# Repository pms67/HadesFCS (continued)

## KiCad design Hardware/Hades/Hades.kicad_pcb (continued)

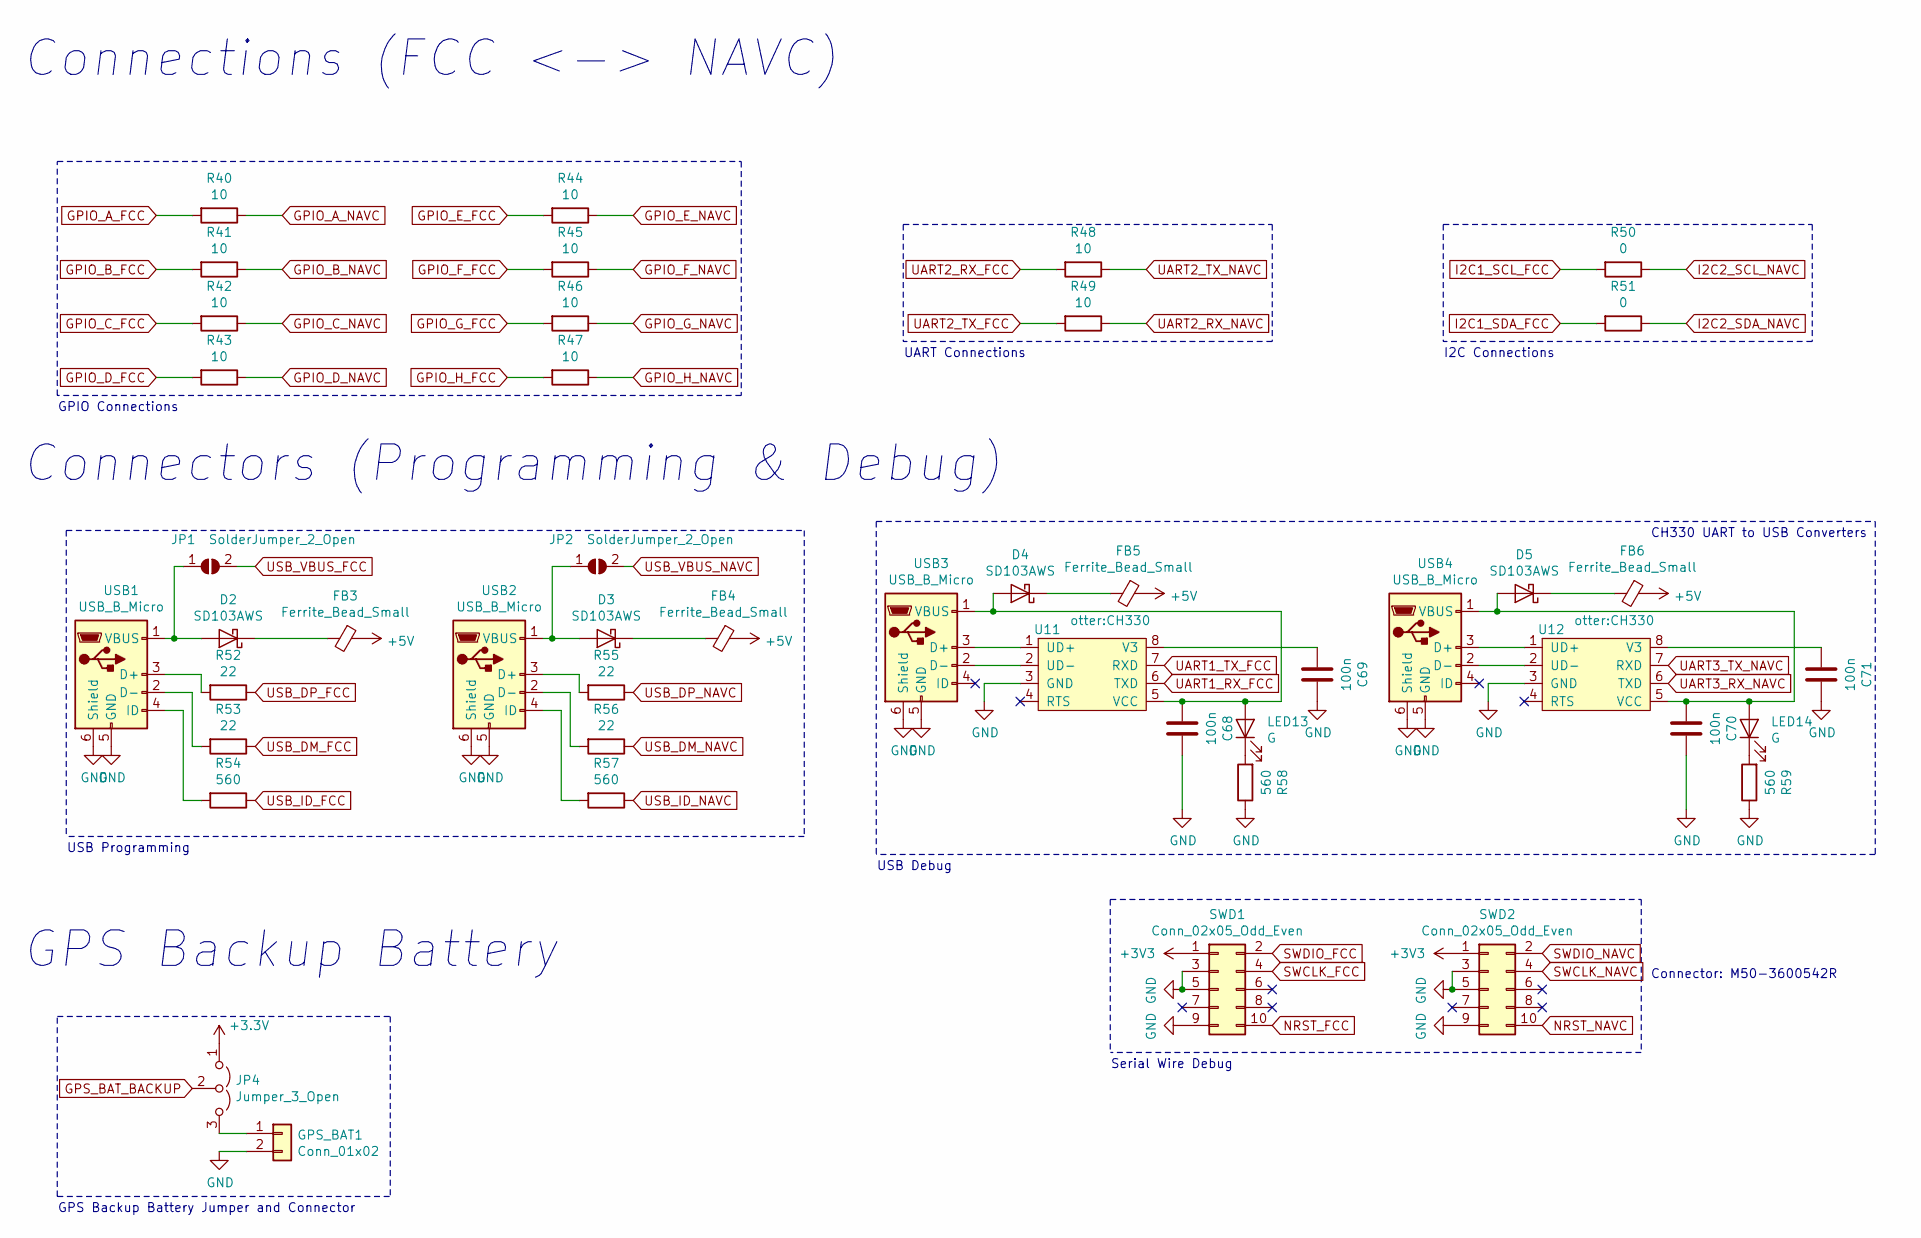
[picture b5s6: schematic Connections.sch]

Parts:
C68, C69, C70, C71: 100n; C_0402_1005Metric
D2, D3, D4, D5: SD103AWS; D_SOD-323
FB3, FB4, FB5, FB6: Ferrite_Bead_Small; L_0402_1005Metric
GPS_BAT1: Conn_01x02; Molex_PicoBlade_53048-0210_1x02_P1.25mm_Horizontal
JP1, JP2: SolderJumper_2_Open; SolderJumper-2_P1.3mm_Open_RoundedPad1.0x1.5mm
JP4: Jumper_3_Open; SolderJumper-3_P1.3mm_Open_RoundedPad1.0x1.5mm
LED13, LED14: G; LED_0603_1608Metric
R40, R41, R42, R43, R44, R45, R46, R47, R48, R49: 10; R_0402_1005Metric
R50, R51: 0; R_0603_1608Metric
R52, R53, R55, R56: 22; R_0402_1005Metric
R54, R57: 560; R_0402_1005Metric
R58, R59: 560; R_0603_1608Metric
SWD1, SWD2: Conn_02x05_Odd_Even; PinHeader_2x05_P1.27mm_Vertical_SMD
U11, U12: otter:CH330; SSOP-8_3.9x5.05mm_P1.27mm
USB1, USB2, USB3, USB4: USB_B_Micro; USB_Micro-B_Wuerth_629105150521_CircularHoles

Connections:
+5V: FB3.1, FB4.1, FB5.1, FB6.1; also elsewhere on the board
GND: C68.1, C69.1, C70.1, C71.1, GPS_BAT1.2, R58.1, R59.1, SWD1.3, SWD1.5, SWD1.9, SWD2.3, SWD2.5, SWD2.9, U11.3 (GND), U12.3 (GND), USB1.5 (GND), USB1.6 (Shield), USB2.5 (GND), USB2.6 (Shield), USB3.5 (GND), USB3.6 (Shield), USB4.5 (GND), USB4.6 (Shield); also elsewhere on the board
GPIO_A_FCC: R40.2; also elsewhere on the board
GPIO_A_NAVC: R40.1; also elsewhere on the board
GPIO_B_FCC: R41.2; also elsewhere on the board
GPIO_B_NAVC: R41.1; also elsewhere on the board
GPIO_C_FCC: R42.2; also elsewhere on the board
GPIO_C_NAVC: R42.1; also elsewhere on the board
GPIO_D_FCC: R43.2; also elsewhere on the board
GPIO_D_NAVC: R43.1; also elsewhere on the board
GPIO_E_FCC: R44.2; also elsewhere on the board
GPIO_E_NAVC: R44.1; also elsewhere on the board
GPIO_F_FCC: R45.2; also elsewhere on the board
GPIO_F_NAVC: R45.1; also elsewhere on the board
GPIO_G_FCC: R46.2; also elsewhere on the board
GPIO_G_NAVC: R46.1; also elsewhere on the board
GPIO_H_FCC: R47.2; also elsewhere on the board
GPIO_H_NAVC: R47.1; also elsewhere on the board
GPS_BAT_BACKUP: JP4.2 (C); also elsewhere on the board
I2C1_SCL_FCC: R50.2; also elsewhere on the board
I2C1_SDA_FCC: R51.2; also elsewhere on the board
I2C2_SCL_NAVC: R50.1; also elsewhere on the board
I2C2_SDA_NAVC: R51.1; also elsewhere on the board
unnamed: C68.2, D4.2 (A), LED13.2 (A), U11.5 (VCC), USB3.1 (VBUS)
unnamed: C69.2, U11.8 (V3)
unnamed: C70.2, D5.2 (A), LED14.2 (A), U12.5 (VCC), USB4.1 (VBUS)
unnamed: C71.2, U12.8 (V3)
unnamed: D2.1 (K), FB3.2
unnamed: D2.2 (A), JP1.1 (A), USB1.1 (VBUS)
unnamed: D3.1 (K), FB4.2
unnamed: D3.2 (A), JP2.1 (A), USB2.1 (VBUS)
unnamed: D4.1 (K), FB5.2
unnamed: D5.1 (K), FB6.2
unnamed 119: GPS_BAT1.1, JP4.3 (B); also elsewhere on the board
unnamed: LED13.1 (K), R58.2
unnamed: LED14.1 (K), R59.2
unnamed: R52.2, USB1.3 (D+)
unnamed: R53.2, USB1.2 (D-)
unnamed: R54.2, USB1.4 (ID)
unnamed: R55.2, USB2.3 (D+)
unnamed: R56.2, USB2.2 (D-)
unnamed: R57.2, USB2.4 (ID)
unnamed: SWD1.1, SWD2.1
unnamed: U11.1 (UD+), USB3.3 (D+)
unnamed: U11.2 (UD-), USB3.2 (D-)
unnamed: U12.1 (UD+), USB4.3 (D+)
unnamed: U12.2 (UD-), USB4.2 (D-)
UART1_RX_FCC: U11.6 (TXD); also elsewhere on the board
UART1_TX_FCC: U11.7 (RXD); also elsewhere on the board
UART2_RX_FCC: R48.2; also elsewhere on the board
UART2_RX_NAVC: R49.1; also elsewhere on the board
UART2_TX_FCC: R49.2; also elsewhere on the board
UART2_TX_NAVC: R48.1; also elsewhere on the board
UART3_RX_NAVC: U12.6 (TXD); also elsewhere on the board
UART3_TX_NAVC: U12.7 (RXD); also elsewhere on the board
USB_DM_FCC: R53.1; also elsewhere on the board
USB_DM_NAVC: R56.1; also elsewhere on the board
USB_DP_FCC: R52.1; also elsewhere on the board
USB_DP_NAVC: R55.1; also elsewhere on the board
USB_ID_FCC: R54.1; also elsewhere on the board
USB_ID_NAVC: R57.1; also elsewhere on the board
USB_VBUS_FCC: JP1.2 (B); also elsewhere on the board
USB_VBUS_NAVC: JP2.2 (B); also elsewhere on the board

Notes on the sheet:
GPIO Connections
UART Connections
I2C Connections
Connections (FCC <-> NAVC)
GPS Backup Battery
GPS Backup Battery Jumper and Connector
Connectors (Programming & Debug)
USB Programming
USB Debug
CH330 UART to USB Converters
Serial Wire Debug
Connector: M50-3600542R

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
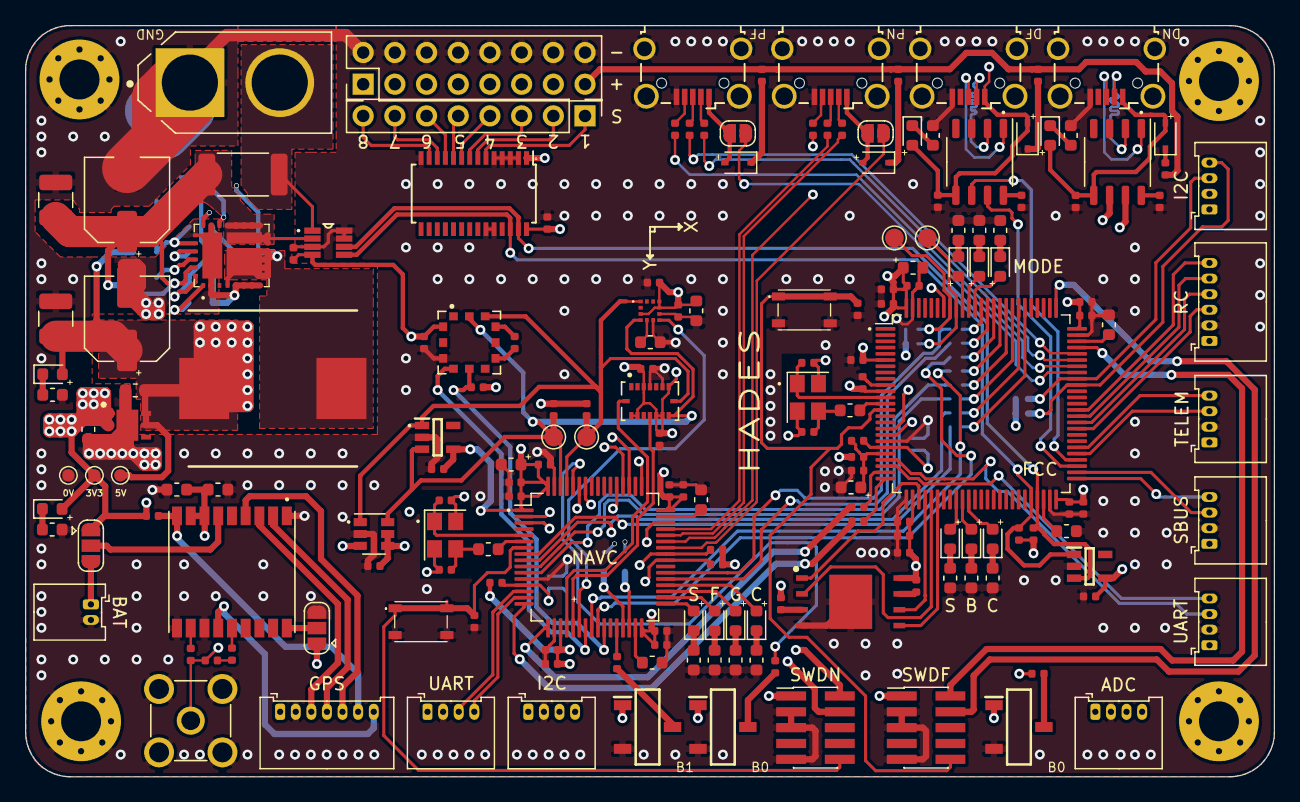
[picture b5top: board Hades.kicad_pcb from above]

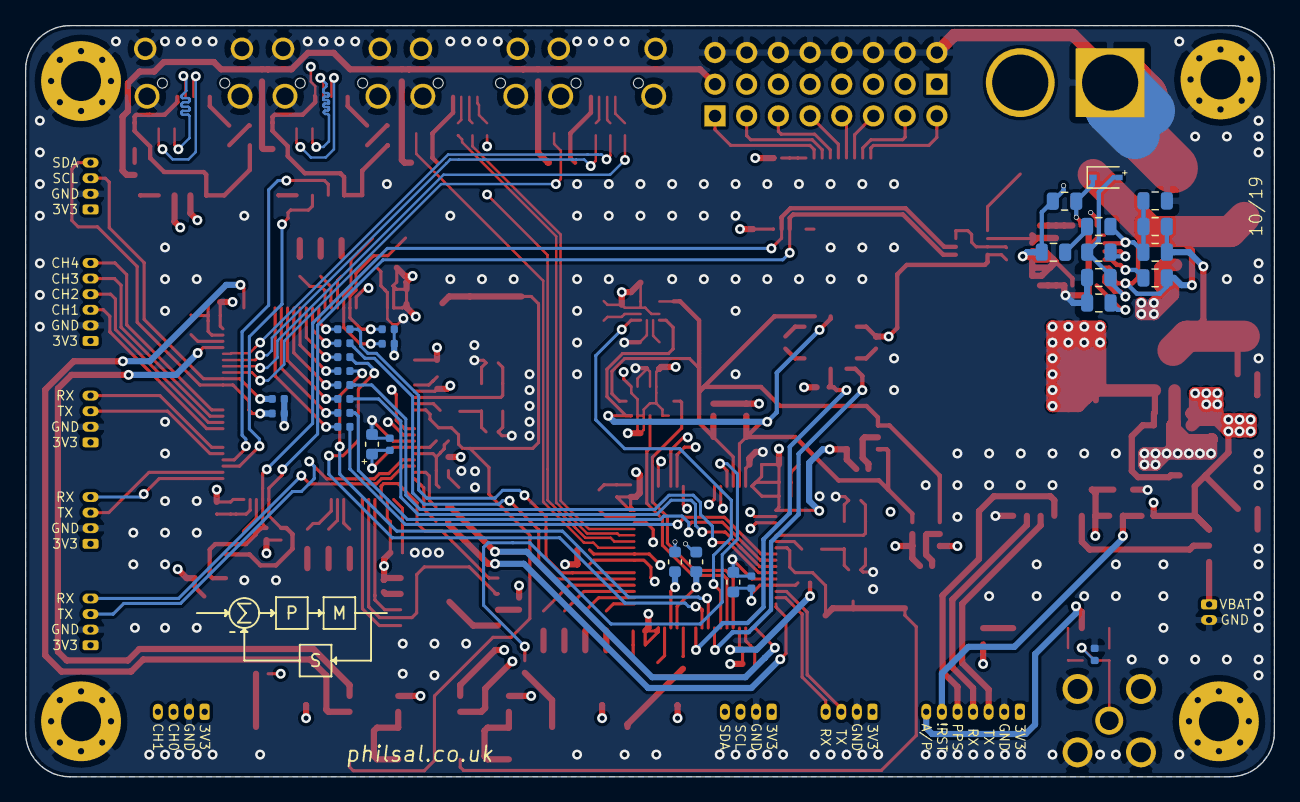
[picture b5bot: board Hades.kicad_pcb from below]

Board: 4 copper layers, 100.1 x 60.2 mm, 211 parts (30 on the bottom side), 174 nets.

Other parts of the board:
5V, 5V#2, 5V#3: TestPoint_Pad_D1.0mm
ADC: Conn_01x04; Molex_PicoBlade_53048-0410_1x04_P1.25mm_Horizontal
BAT: Conn_01x02; Molex_PicoBlade_53048-0210_1x02_P1.25mm_Horizontal
FCC: STM32H753VITx; LQFP-100_14x14mm_P0.5mm
GPS: Conn_01x07; Molex_PicoBlade_53048-0710_1x07_P1.25mm_Horizontal
I2C, I2C#2: Conn_01x04; Molex_PicoBlade_53048-0410_1x04_P1.25mm_Horizontal
NAVC: STM32F405RGTx; LQFP-64_10x10mm_P0.5mm
RC: Conn_01x06; Molex_PicoBlade_53048-0610_1x06_P1.25mm_Horizontal
SBUS: Conn_01x04; Molex_PicoBlade_53048-0410_1x04_P1.25mm_Horizontal
SWDF: Conn_02x05_Odd_Even; PinHeader_2x05_P1.27mm_Vertical_SMD
SWDN: Conn_02x05_Odd_Even; PinHeader_2x05_P1.27mm_Vertical_SMD
TELEM: Conn_01x04; Molex_PicoBlade_53048-0410_1x04_P1.25mm_Horizontal
UART: Conn_01x04; Molex_PicoBlade_53048-0410_1x04_P1.25mm_Horizontal
UART#2: Conn_01x04; Molex_PicoBlade_53048-0410_1x04_P1.25mm_Horizontal

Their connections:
+5V: 5V#3.1; also elsewhere on the board
ADC3_0_FCC: ADC.3, FCC.17
ADC3_1_FCC: ADC.4, FCC.18
BAR_NRST_NAVC: NAVC.26; also elsewhere on the board
BOOT0_FCC: FCC.94; also elsewhere on the board
BOOT0_NAVC: NAVC.60; also elsewhere on the board
BOOT1_NAVC: NAVC.28; also elsewhere on the board
GND: 5V.1, ADC.2, BAT.2, FCC.10, FCC.19, FCC.26, FCC.49, FCC.74, FCC.99, GPS.2, I2C.2, I2C#2.2, NAVC.12, NAVC.18, NAVC.63, RC.2, SBUS.2, SWDF.3, SWDF.5, SWDF.9, SWDN.3, SWDN.5, SWDN.9, TELEM.2, UART.2, UART#2.2; also elsewhere on the board
GPIO_A_FCC: FCC.81; also elsewhere on the board
GPIO_A_NAVC: NAVC.8; also elsewhere on the board
GPIO_B_FCC: FCC.82; also elsewhere on the board
GPIO_B_NAVC: NAVC.9; also elsewhere on the board
GPIO_C_FCC: FCC.83; also elsewhere on the board
GPIO_C_NAVC: NAVC.10; also elsewhere on the board
GPIO_D_FCC: FCC.84; also elsewhere on the board
GPIO_D_NAVC: NAVC.11; also elsewhere on the board
GPIO_E_FCC: FCC.85; also elsewhere on the board
GPIO_E_NAVC: NAVC.24; also elsewhere on the board
GPIO_F_FCC: FCC.86; also elsewhere on the board
GPIO_F_NAVC: NAVC.25; also elsewhere on the board
GPIO_G_FCC: FCC.87; also elsewhere on the board
GPIO_G_NAVC: NAVC.37; also elsewhere on the board
GPIO_H_FCC: FCC.88; also elsewhere on the board
GPIO_H_NAVC: NAVC.38; also elsewhere on the board
GPS_LNA_EN_NAVC: GPS.7, NAVC.2; also elsewhere on the board
GPS_NRST_NAVC: GPS.6, NAVC.3; also elsewhere on the board
GPS_PPS_NAVC: GPS.5, NAVC.53; also elsewhere on the board
HSE_IN_FCC: FCC.12; also elsewhere on the board
HSE_IN_NAVC: NAVC.5; also elsewhere on the board
HSE_OUT_FCC: FCC.13; also elsewhere on the board
HSE_OUT_NAVC: NAVC.6; also elsewhere on the board
I2C1_SCL_FCC: FCC.92; also elsewhere on the board
I2C1_SCL_NAVC: NAVC.61; also elsewhere on the board
I2C1_SDA_FCC: FCC.93; also elsewhere on the board
I2C1_SDA_NAVC: NAVC.62; also elsewhere on the board
I2C2_SCL_FCC: FCC.46; also elsewhere on the board
I2C2_SCL_NAVC: NAVC.29; also elsewhere on the board
I2C2_SDA_FCC: FCC.47; also elsewhere on the board
I2C2_SDA_NAVC: NAVC.30; also elsewhere on the board
I2C3_SCL_FCC: FCC.67, I2C.3; also elsewhere on the board
I2C3_SCL_NAVC: I2C#2.3, NAVC.41; also elsewhere on the board
I2C3_SDA_FCC: FCC.66, I2C.4; also elsewhere on the board
I2C3_SDA_NAVC: I2C#2.4, NAVC.40; also elsewhere on the board
INT_ACC_NAVC: NAVC.20; also elsewhere on the board
INT_BAR_NAVC: NAVC.23; also elsewhere on the board
INT_GYR_NAVC: NAVC.21; also elsewhere on the board
INT_MAG_NAVC: NAVC.22; also elsewhere on the board
LED_A_FCC: FCC.34; also elsewhere on the board
LED_A_NAVC: NAVC.33; also elsewhere on the board
LED_B_FCC: FCC.35; also elsewhere on the board
LED_B_NAVC: NAVC.34; also elsewhere on the board
LED_C_FCC: FCC.36; also elsewhere on the board
LED_C_NAVC: NAVC.35; also elsewhere on the board
LED_D_FCC: FCC.89; also elsewhere on the board
LED_D_NAVC: NAVC.36; also elsewhere on the board
LED_E_FCC: FCC.90; also elsewhere on the board
LED_F_FCC: FCC.91; also elsewhere on the board
NRST_FCC: FCC.14, SWDF.10; also elsewhere on the board
NRST_NAVC: NAVC.7, SWDN.10; also elsewhere on the board
unnamed 65: FCC.48; also elsewhere on the board
unnamed 66: FCC.73; also elsewhere on the board
unnamed 68: NAVC.31; also elsewhere on the board
unnamed 69: NAVC.47; also elsewhere on the board
unnamed 119: BAT.1; also elsewhere on the board
SPI1_CS_FLASH_FCC: FCC.28; also elsewhere on the board
SPI1_MISO_FCC: FCC.30; also elsewhere on the board
SPI1_MOSI_FCC: FCC.31; also elsewhere on the board
SPI1_SCK_FCC: FCC.29; also elsewhere on the board
SWCLK_FCC: FCC.76, SWDF.4
SWCLK_NAVC: NAVC.49, SWDN.4
SWDIO_FCC: FCC.72, SWDF.2
SWDIO_NAVC: NAVC.46, SWDN.2
TIM4_CH1_FCC: FCC.59, RC.3
TIM4_CH2_FCC: FCC.60, RC.4
TIM4_CH3_FCC: FCC.61, RC.5
TIM4_CH4_FCC: FCC.62, RC.6
UART1_RX_FCC: FCC.54; also elsewhere on the board
UART1_RX_NAVC: GPS.4, NAVC.59; also elsewhere on the board
UART1_TX_FCC: FCC.53; also elsewhere on the board
UART1_TX_NAVC: GPS.3, NAVC.58; also elsewhere on the board
UART2_RX_FCC: FCC.25; also elsewhere on the board
UART2_RX_NAVC: NAVC.17; also elsewhere on the board
UART2_TX_FCC: FCC.24; also elsewhere on the board
UART2_TX_NAVC: NAVC.16; also elsewhere on the board
UART3_RX_FCC: FCC.56, TELEM.4
UART3_RX_NAVC: NAVC.52; also elsewhere on the board
UART3_TX_FCC: FCC.55, TELEM.3
UART3_TX_NAVC: NAVC.51; also elsewhere on the board
UART4_RX_FCC: FCC.23, UART.4
UART4_RX_NAVC: NAVC.15, UART#2.4
UART4_TX_FCC: FCC.22, UART.3
UART4_TX_NAVC: NAVC.14, UART#2.3
UART5_RX_FCC: FCC.51, SBUS.4
UART5_TX_FCC: FCC.52, SBUS.3
USB_DM_FCC: FCC.70; also elsewhere on the board
USB_DM_NAVC: NAVC.44; also elsewhere on the board
USB_DP_FCC: FCC.71; also elsewhere on the board
USB_DP_NAVC: NAVC.45; also elsewhere on the board
USB_ID_FCC: FCC.69; also elsewhere on the board
USB_ID_NAVC: NAVC.43; also elsewhere on the board
USB_VBUS_FCC: FCC.68; also elsewhere on the board
USB_VBUS_NAVC: NAVC.42; also elsewhere on the board
VDDA_FCC: FCC.21; also elsewhere on the board
VDDA_NAVC: NAVC.13; also elsewhere on the board
VREF+_FCC: FCC.20; also elsewhere on the board

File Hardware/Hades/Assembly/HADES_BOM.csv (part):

Ref Des,Qty,Manufacturer,Mfr Part #,Value,Package,Type,Your Instructions / Notes
ANT1,1,TE Connectivity,5-1814832-1,5-1814832-1,5-1814832-1:TE_5-1814832-1,THT,"50 Ohm SMA, see 3D picture for orientation"
BAT1,1,SparkFun,PRT-10474,XT60-M,XT60-M:AMASS_XT60-M,THT,"Male XT-60 Connector, NEGATIVE TERMINAL indicated by DOT on silkscreen, SEE 3D PICTURE FOR REFERENCE!"
"C1, C8",2,Panasonic,EEE-FPV101XAV,100u,Capacitor_SMD:C_Elec_6.3x7.7,SMD,"Low ESR, High Ripple Current, Al Electrolytic, 35V, Polarity indicated by + on silkscreen"
"C2, C9",2,Taiyo Yuden,GMK325BJ226MM-T,22u,Capacitor_SMD:C_1210_3225Metric,SMD,"Low ESR, 35V"
"C3, C4",2,KEMET,C0805C225K4REC7210,2u2,Capacitor_SMD:C_0805_2012Metric,SMD,at least 10V rated
"C5, C6",2,KEMET,C0805X104K5RAC3316,100n,Capacitor_SMD:C_0805_2012Metric,SMD,at least 10V rated
C7,1,KEMET,C0805C472J3GEC7210,4n7,Capacitor_SMD:C_0805_2012Metric,SMD,at least 10V rated
"C10, C16, C17, C18, C19, C20, C21, C22, C23, C24, C25, C26, C28, C30, C31, C34, C35, C36, C40, C41, C42, C43, C44, C45, C46, C47, C48, C49, C51, C54, C55, C56, C58, C60, C61, C63, C68, C69, C70, C71, ",40,Murata Electronics,GRM155R61H104JE14D,100n,Capacitor_SMD:C_0402_1005Metric,SMD,at least 10V rated
"C11, C12, C62",3,Murata Electronics,GRM188R61E106KA73D,10u,Capacitor_SMD:C_0603_1608Metric,SMD,at least 10V rated
"C15, C39",2,AVX,F381A106MMAAH1,10u,Capacitor_SMD:C_0603_1608Metric,SMD,"Tantalum, Polarity indicated by + on silkscreen"
"C13, C14,  C37, C38,",4,Yageo,CC0603KRX5R9BB225,2u2,Capacitor_SMD:C_0603_1608Metric,SMD,ESR < 100mOhms!
"C27, C29, C50",3,AVX,TACL105K010RTA,1u,Capacitor_SMD:C_0603_1608Metric,SMD,"Tantalum, Polarity indicated by + on silkscreen"
"C64, C65",2,KEMET,C0603C105Z3VACTU,1u,Capacitor_SMD:C_0603_1608Metric,SMD,at least 10V rated
"C32, C33, C52, C53, ",4,AVX,04025A100JAT2A,10p,Capacitor_SMD:C_0402_1005Metric,SMD,at least 10V rated
"C57, ",1,KEMET,C0402C102J5GAC7411,1n,Capacitor_SMD:C_0402_1005Metric,SMD,at least 10V rated
"C59, ",1,KEMET,C0603C224K4RAC7411,220n,Capacitor_SMD:C_0603_1608Metric,SMD,at least 10V rated
C66,1,KEMET,C0402C220J8GACTU,22p,Capacitor_SMD:C_0402_1005Metric,SMD,at least 10V rated
"C67, ",1,KEMET,C0402C103J3RACAUTO,10n,Capacitor_SMD:C_0402_1005Metric,SMD,at least 10V rated
"D1, D2, D3, D5, D4, ",5,Diodes Incorporated,SD103AWS-7-F,SD103AWS,Diode_SMD:D_SOD-323,SMD,"Schottky diode, Polarity indicated by + on silkscreen"
"FB1, FB2, FB3, FB4, FB5, FB6, ",6,TDK,MPZ1005S121HT000,Ferrite_Bead_Small,Inductor_SMD:L_0402_1005Metric,SMD,"Ferrite bead, 1.5A current rating"
"FCC1, ",1,STMicroelectronics,STM32H753VIT6,STM32H753VITx,Package_QFP:LQFP-100_14x14mm_P0.5mm,SMD,"Pin 1 indicated by DOT on silkscreen, WATCH FOR PIN 1 ON DATASHEET (LQFP-100)"
"GPS_BAT1, ",1,Molex,53048-0210,Conn_01x02,Connector_Molex:Molex_PicoBlade_53048-0210_1x02_P1.25mm_Horizontal,THT,Watch orientation! See attached 3D picture!
"GPS_NAVC1, ",1,Molex,53048-0710,Conn_01x07,Connector_Molex:Molex_PicoBlade_53048-0710_1x07_P1.25mm_Horizontal,THT,Watch orientation! See attached 3D picture!
"HSE1, HSE2",2,ABRACON,ABM8G-25.000MHZ-4Y-T3,25MHz,Crystal:Crystal_SMD_Abracon_ABM8G-4Pin_3.2x2.5mm,SMD,"Pin 1 indicated by DOT on silkscreen, WATCH FOR PIN 1 ON DATASHEET"
L1,1,Bourns,SRP1265A-150M,15u,SRP1265A-150M:INDPM135125X650N,SMD,DC Current Rating at least 9A
L2,1,Murata Electronics,LQW15AN27NJ8ZD,27n,Inductor_SMD:L_0402_1005Metric,SMD,
"LED1, LED2, LED13, LED14, ",4,Dialight,599-0081-007F,GREEN,LED_SMD:LED_0603_1608Metric,SMD,"Green LED, Polarity indicated by + on silkscreen"
"LED3, LED4, LED9, LED10, ",4,Dialight,599-0010-007F,RED,LED_SMD:LED_0603_1608Metric,SMD,"Red LED, Polarity indicated by + on silkscreen"
"LED5, LED11, ",2,Dialight,599-0040-007F,YELLOW,LED_SMD:LED_0603_1608Metric,SMD,"Yellow LED, Polarity indicated by + on silkscreen"
"LED6, LED7, LED8, LED12, ",4,Dialight,599-0091-007F,BLUE,LED_SMD:LED_0603_1608Metric,SMD,"Blue LED, Polarity indicated by + on silkscreen"
"NAVC1, ",1,STMicroelectronics,STM32F405RGT6,STM32F405RGTx,Package_QFP:LQFP-64_10x10mm_P0.5mm,SMD,"Pin 1 indicated by DOT on silkscreen, WATCH FOR PIN 1 ON DATASHEET (LQFP-64)"
"PWM_POW1, ",1,Samtec,HTSW-108-07-T-T,Conn_02x08_Odd_Even,Connector_PinHeader_2.54mm:PinHeader_2x08_P2.54mm_Vertical,THT,"3 Rows 8 Columns (24 Positions total), 2.54mm Pitch, Vertical Male Header Pins"
"R1, ",1,Yageo,PE2512FKE7W0R01Z,0.01,Resistor_SMD:R_2512_6332Metric,SMD,1W 1% 10mOhms 2512 Current Sense Resistor
"R2, R3, ",2,Panasonic,ERJ-T06J103V,10k,Resistor_SMD:R_0805_2012Metric,SMD,1/4W
"R4, ",1,Panasonic,ERJ-PB6B1962V,19k6,Resistor_SMD:R_0805_2012Metric,SMD,"1%, 1/8W"
"R5, ",1,KOA Speer,RK73H2ATTD6R80F,6k8,Resistor_SMD:R_0805_2012Metric,SMD,"1%, 1/8W"
"R6, ",1,KOA Speer,RK73H2ATTD1301F,1k3,Resistor_SMD:R_0805_2012Metric,SMD,"1%, 1/8W"
"R7, R58, R59, ",3,Panasonic,ERJ-PA3F5600V,560,Resistor_SMD:R_0603_1608Metric,SMD,1/4W
"R8, ",1,Panasonic,ERJ-PA3F2400V,240,Resistor_SMD:R_0603_1608Metric,SMD,1/4W
"R9, R10, R11, R12, R13, R14, R28, R29, R30, R31, ",10,KOA Speer,SG73P1ETTP4701F,4k7,Resistor_SMD:R_0402_1005Metric,SMD,1/4W
"R15, R16, R17, R33, R34, R35, ",6,Panasonic,ERJ-PA3D3300V,330,Resistor_SMD:R_0603_1608Metric,SMD,1/4W
"R18, R19, R20, R36, ",4,Panasonic,ERJ-PA3D1000V,100,Resistor_SMD:R_0603_1608Metric,SMD,1/4W
"R21, ",1,Panasonic,ERA-2AED470X,47,Resistor_SMD:R_0402_1005Metric,SMD,1/8W
"R22, R24, R25, R26, R27, R37, R38, ",7,TE Connectivity / Holsworthy,CRGP0402F10K,10k,Resistor_SMD:R_0402_1005Metric,SMD,1/4W
"R23, R32, ",2,Panasonic,ERJ-PA3F6200V,620,Resistor_SMD:R_0603_1608Metric,SMD,1/4W
"R39, R40, R41, R42, R43, R44, R45, R46, R47, R48, R49, ",11,Panasonic,ERA-2AKD100X,10,Resistor_SMD:R_0402_1005Metric,SMD,1/8W
"R50, R51, ",2,Vishay / Dale,RCS06030000Z0EC,0,Resistor_SMD:R_0603_1608Metric,SMD,1/8W
"R52, R53, R55, R56, ",4,Panasonic,ERA-2AKD220X,22,Resistor_SMD:R_0402_1005Metric,SMD,1/8W
"R54, R57, ",2,TE Connectivity / Holsworthy,CRGP0402F560R,560,Resistor_SMD:R_0402_1005Metric,SMD,1/8W
"RCIN_FCC1, ",1,Molex,53048-0610,Conn_01x06,Connector_Molex:Molex_PicoBlade_53048-0610_1x06_P1.25mm_Horizontal,THT,Watch orientation! See attached 3D picture!
"REG1, ",1,Microchip Technology,MIC26903YJL-TR,MIC26903YJL-TR,MLF-28,SMD,Pin 1 indicated by DOT on silkscreen
"REG2, ",1,STMicroelectronics,LD39200PU33R,LD39200PU33R,DFN-6,SMD,Pin 1 indicated by DOT on silkscreen
"SW1, SW5, ",2,ALPS,SKRPANE010,SKRPANE010,SKRPANE010:SKRPADE010,SMD,See attached 3D picture for orientation
"SW2, SW3, SW4, ",3,C&K,TDD01H0SB1R,TDD01H0SB1R,TDD01H0SB1R:SOT175P420X230-3N,SMD,See attached 3D picture for orientation
"SWD1, SWD2, ",2,Harwin,M50-3600542R,Conn_02x05_Odd_Even,Connector_PinHeader_1.27mm:PinHeader_2x05_P1.27mm_Vertical_SMD,SMD,"2 Rows, 5 Columns (10 Positions), SMD 1.27mm pitch, See attached 3D picture for orientation"
"U1, ",1,Texas Instruments,INA219AIDCNR,INA219AIDCNR,SOT-23-8,SMD,Pin 1 indicated by DOT on silkscreen
"U2, ",1,NXP Semiconductors,"PCA9685PW,118",PCA9685PW,TSSOP28,SMD,Pin 1 indicated by DOT on silkscreen
"U3, U9, ",2,Microchip Technology,24CW1280T-I/OT,24CW1280T-I_OT,SOT-23-5,SMD,Pin 1 indicated by DOT on silkscreen
"U4, ",1,Winbond,W25N01GVZEIG TR,W25N01GVZEIG_TR,WSON 8x6-mm ,SMD,Pin 1 indicated by DOT on silkscreen
"U5, ",1,Bosch Sensortec,BMI088,BMI088,LGA-16,SMD,Pin 1 indicated by DOT on silkscreen
"U6, ",1,Texas Instruments,TMP100NA/3K,TMP100,SOT-23-6,SMD,Pin 1 indicated by DOT on silkscreen
"U7, ",1,Honeywell,MPRLS0025PA00001A,MPRLS0025PA00001A,MPRLS0025PA00001A:XDCR_MPRLS0025PA00001A,SMD,Pin 1 indicated by DOT on silkscreen
"U8, ",1,STMicroelectronics,IIS2MDCTR,IIS2MDCTR,LGA-12 2.0 x 2.0 x 0.7 mm,SMD,Pin 1 indicated by DOT on silkscreen
"U10, ",1,u-blox,MAX-8Q,u-blox MAX-8Q,MODULE-GPS-SMD-MAX-7Q-0_18P-9.6X10MM_:GPS18P-SMD-1.1-10X9.6MM,SMD,"Pin 1 indicated by DOT on silkscreen, Datasheet: https://www.u-blox.com/sites/default/files/MAX-8_DataSheet_%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"
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
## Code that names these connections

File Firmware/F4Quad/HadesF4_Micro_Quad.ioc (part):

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Mcu.Name=STM32F405RGTx
Mcu.Package=LQFP64
Mcu.UserName=STM32F405RGTx
PA0-WKUP.GPIOParameters=GPIO_Label,GPIO_ModeDefaultEXTI
PA0-WKUP.GPIO_Label=RC1
PA0-WKUP.GPIO_ModeDefaultEXTI=GPIO_MODE_IT_RISING_FALLING
PA0-WKUP.Signal=GPXTI0
PA1.GPIOParameters=GPIO_Label,GPIO_ModeDefaultEXTI
PA1.GPIO_Label=RC2
PA1.GPIO_ModeDefaultEXTI=GPIO_MODE_IT_RISING_FALLING
PA1.Signal=GPXTI1
PA10.Mode=Asynchronous
PA10.Signal=USART1_RX
PA13.Mode=Serial_Wire
PA13.Signal=SYS_JTMS-SWDIO
PA14.Mode=Serial_Wire
PA14.Signal=SYS_JTCK-SWCLK
PA2.Mode=Asynchronous
PA2.Signal=USART2_TX
PA3.Mode=Asynchronous
PA3.Signal=USART2_RX
PA4.GPIOParameters=GPIO_Label
PA4.GPIO_Label=SPI1_CS
PA4.Signal=GPIO_Output
PA5.Mode=Full_Duplex_Master
PA5.Signal=SPI1_SCK
PA6.Mode=Full_Duplex_Master
PA6.Signal=SPI1_MISO
PA7.Mode=Full_Duplex_Master
PA7.Signal=SPI1_MOSI
PA8.Mode=I2C
PA8.Signal=I2C3_SCL
PA9.Mode=Asynchronous
PA9.Signal=USART1_TX
PB10.Mode=Asynchronous
PB10.Signal=USART3_TX
PB11.Mode=Asynchronous
PB11.Signal=USART3_RX
PB13.Mode=Full_Duplex_Master
PB13.Signal=SPI2_SCK
PB14.Mode=Full_Duplex_Master
PB14.Signal=SPI2_MISO
PB15.Mode=Full_Duplex_Master
PB15.Signal=SPI2_MOSI
PB3.GPIOParameters=GPIO_Label
PB3.GPIO_Label=SPI3_CSACC
PB3.Signal=GPIO_Output
PB4.GPIOParameters=GPIO_Label
PB4.GPIO_Label=SPI3_CSGYR
PB4.Signal=GPIO_Output
PB5.GPIOParameters=GPIO_Label
PB5.GPIO_Label=SPI3_CSMAG
PB5.Signal=GPIO_Output
PB6.GPIOParameters=GPIO_Label,GPIO_ModeDefaultEXTI
PB6.GPIO_Label=RC3
PB6.GPIO_ModeDefaultEXTI=GPIO_MODE_IT_RISING_FALLING
PB6.Signal=GPXTI6
PB7.GPIOParameters=GPIO_Label,GPIO_ModeDefaultEXTI
PB7.GPIO_Label=RC4
PB7.GPIO_ModeDefaultEXTI=GPIO_MODE_IT_RISING_FALLING
PB7.Signal=GPXTI7
PB8.Mode=I2C
PB8.Signal=I2C1_SCL
PB9.Mode=I2C
PB9.Signal=I2C1_SDA
PC0.GPIOParameters=GPIO_Label
PC0.GPIO_Label=LED_A
PC0.Signal=GPIO_Output
PC1.GPIOParameters=GPIO_Label
PC1.GPIO_Label=LED_B
PC1.Signal=GPIO_Output
PC10.Mode=Full_Duplex_Master
PC10.Signal=SPI3_SCK
PC11.Mode=Full_Duplex_Master
PC11.Signal=SPI3_MISO
PC12.Mode=Full_Duplex_Master
PC12.Signal=SPI3_MOSI
PC13-ANTI_TAMP.GPIOParameters=GPIO_Label
PC13-ANTI_TAMP.GPIO_Label=INT_ACC
PC13-ANTI_TAMP.Signal=GPIO_Input
PC14-OSC32_IN.GPIOParameters=GPIO_Label
PC14-OSC32_IN.GPIO_Label=INT_GYR
PC14-OSC32_IN.Signal=GPIO_Input
PC15-OSC32_OUT.GPIOParameters=GPIO_Label
PC15-OSC32_OUT.GPIO_Label=INT_MAG
PC15-OSC32_OUT.Signal=GPIO_Input
PC2.GPIOParameters=GPIO_Label
PC2.GPIO_Label=LED_C
PC2.Signal=GPIO_Output
PC3.GPIOParameters=GPIO_Label
PC3.GPIO_Label=LED_D
PC3.Signal=GPIO_Output
PC4.GPIOParameters=GPIO_Label
PC4.GPIO_Label=FLASH_NWP
PC4.Signal=GPIO_Output
PC5.GPIOParameters=GPIO_Label
PC5.GPIO_Label=FLASH_NHOLD
PC5.Signal=GPIO_Output
PC6.GPIOParameters=GPIO_Label
PC6.GPIO_Label=SPI2_CS
PC6.Signal=GPIO_Output
PC7.GPIOParameters=GPIO_Label
PC7.GPIO_Label=INT_BAR
PC7.Signal=GPIO_Input
PC8.GPIOParameters=GPIO_Label
PC8.GPIO_Label=BAR_NRST
PC8.Signal=GPIO_Output
PC9.Mode=I2C
PC9.Signal=I2C3_SDA
PH0-OSC_IN.Mode=HSE-External-Oscillator
PH0-OSC_IN.Signal=RCC_OSC_IN
PH1-OSC_OUT.Mode=HSE-External-Oscillator
PH1-OSC_OUT.Signal=RCC_OSC_OUT
RCC.HSE_VALUE=16000000
RCC.SYSCLKFreq_VALUE=168000000
RCC.SYSCLKSource=RCC_SYSCLKSOURCE_PLLCLK
board=custom

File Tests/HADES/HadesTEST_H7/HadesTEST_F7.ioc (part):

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Mcu.Name=STM32H753VITx
Mcu.Package=LQFP100
Mcu.UserName=STM32H753VITx
PA0.Mode=Asynchronous
PA0.Signal=UART4_TX
PA1.Mode=Asynchronous
PA1.Signal=UART4_RX
PA13\ (JTMS/SWDIO).Mode=Serial_Wire
PA13\ (JTMS/SWDIO).Signal=DEBUG_JTMS-SWDIO
PA14\ (JTCK/SWCLK).Mode=Serial_Wire
PA14\ (JTCK/SWCLK).Signal=DEBUG_JTCK-SWCLK
PA2.Mode=Asynchronous
PA2.Signal=USART2_TX
PA3.Mode=Asynchronous
PA3.Signal=USART2_RX
PA4.GPIOParameters=GPIO_Label
PA4.GPIO_Label=SPI1_CS_FLASH
PA4.Signal=GPIO_Output
PA5.Mode=Full_Duplex_Master
PA5.Signal=SPI1_SCK
PA6.Mode=Full_Duplex_Master
PA6.Signal=SPI1_MISO
PA7.Mode=Full_Duplex_Master
PA7.Signal=SPI1_MOSI
PA8.Mode=I2C
PA8.Signal=I2C3_SCL
PB0.GPIOParameters=GPIO_Label
PB0.GPIO_Label=LEDA
PB0.Signal=GPIO_Output
PB1.GPIOParameters=GPIO_Label
PB1.GPIO_Label=LEDB
PB1.Signal=GPIO_Output
PB10.Mode=I2C
PB10.Signal=I2C2_SCL
PB11.Mode=I2C
PB11.Signal=I2C2_SDA
PB12.Mode=Asynchronous
PB12.Signal=UART5_RX
PB13.Mode=Asynchronous
PB13.Signal=UART5_TX
PB14.Mode=Asynchronous
PB14.Signal=USART1_TX
PB15.Mode=Asynchronous
PB15.Signal=USART1_RX
PB2.GPIOParameters=GPIO_Label
PB2.GPIO_Label=LEDC
PB2.Signal=GPIO_Output
PB3\ (JTDO/TRACESWO).GPIOParameters=GPIO_Label
PB3\ (JTDO/TRACESWO).GPIO_Label=LEDD
PB3\ (JTDO/TRACESWO).Signal=GPIO_Output
PB4\ (NJTRST).GPIOParameters=GPIO_Label
PB4\ (NJTRST).GPIO_Label=LEDE
PB4\ (NJTRST).Signal=GPIO_Output
PB5.GPIOParameters=GPIO_Label
PB5.GPIO_Label=LEDF
PB5.Signal=GPIO_Output
PB6.Mode=I2C
PB6.Signal=I2C1_SCL
PB7.Mode=I2C
PB7.Signal=I2C1_SDA
PC2_C.Mode=IN0-Single-Ended
PC2_C.Signal=ADC3_INP0
PC3_C.Mode=IN1-Single-Ended
PC3_C.Signal=ADC3_INP1
PC9.Mode=I2C
PC9.Signal=I2C3_SDA
PD0.GPIOParameters=GPIO_Label
PD0.GPIO_Label=NAVCRXA
PD0.Signal=GPIO_Output
PD1.GPIOParameters=GPIO_Label
PD1.GPIO_Label=NAVCRXB
PD1.Signal=GPIO_Output
PD12.Signal=S_TIM4_CH1
PD13.Signal=S_TIM4_CH2
PD14.Signal=S_TIM4_CH3
PD15.Signal=S_TIM4_CH4
PD2.GPIOParameters=GPIO_Label
PD2.GPIO_Label=NAVCRXC
PD2.Signal=GPIO_Output
PD3.GPIOParameters=GPIO_Label
PD3.GPIO_Label=NAVRXD
PD3.Signal=GPIO_Output
PD4.GPIOParameters=GPIO_Label
PD4.GPIO_Label=NAVCTXA
PD4.Signal=GPIO_Input
PD5.GPIOParameters=GPIO_Label
PD5.GPIO_Label=NAVCTXB
PD5.Signal=GPIO_Input
PD6.GPIOParameters=GPIO_Label
PD6.GPIO_Label=NAVCTXC
PD6.Signal=GPIO_Input
PD7.GPIOParameters=GPIO_Label
PD7.GPIO_Label=NAVCTXD
PD7.Signal=GPIO_Input
PD8.Mode=Asynchronous
PD8.Signal=USART3_TX
PD9.Mode=Asynchronous
PD9.Signal=USART3_RX
PH0-OSC_IN\ (PH0).Mode=HSE-External-Oscillator
PH0-OSC_IN\ (PH0).Signal=RCC_OSC_IN
PH1-OSC_OUT\ (PH1).Mode=HSE-External-Oscillator
PH1-OSC_OUT\ (PH1).Signal=RCC_OSC_OUT
RCC.SYSCLKFreq_VALUE=450000000
RCC.SYSCLKSource=RCC_SYSCLKSOURCE_PLLCLK
board=custom

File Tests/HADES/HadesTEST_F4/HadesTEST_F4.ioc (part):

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Mcu.Name=STM32F405RGTx
Mcu.Package=LQFP64
Mcu.UserName=STM32F405RGTx
PA10.Mode=OTG/Dual_Role_Device
PA10.Signal=USB_OTG_FS_ID
PA11.Mode=OTG/Dual_Role_Device
PA11.Signal=USB_OTG_FS_DM
PA12.Mode=OTG/Dual_Role_Device
PA12.Signal=USB_OTG_FS_DP
PA13.Mode=Serial_Wire
PA13.Signal=SYS_JTMS-SWDIO
PA14.Mode=Serial_Wire
PA14.Signal=SYS_JTCK-SWCLK
PA2.Mode=Asynchronous
PA2.Signal=USART2_TX
PA3.Mode=Asynchronous
PA3.Signal=USART2_RX
PA4.GPIOParameters=GPIO_Label
PA4.GPIO_Label=INTACC
PA4.Signal=GPIO_Input
PA5.GPIOParameters=GPIO_Label
PA5.GPIO_Label=INTGYR
PA5.Signal=GPIO_Input
PA6.GPIOParameters=GPIO_Label
PA6.GPIO_Label=INTMAG
PA6.Signal=GPIO_Input
PA7.GPIOParameters=GPIO_Label
PA7.GPIO_Label=INTBAR
PA7.Signal=GPIO_Input
PA8.Mode=I2C
PA8.Signal=I2C3_SCL
PA9.Mode=Activate_VBUS
PA9.Signal=USB_OTG_FS_VBUS
PB0.GPIOParameters=GPIO_PuPd,GPIO_Label
PB0.GPIO_Label=BARNRST
PB0.GPIO_PuPd=GPIO_PULLUP
PB0.Signal=GPIO_Output
PB10.Mode=I2C
PB10.Signal=I2C2_SCL
PB11.Mode=I2C
PB11.Signal=I2C2_SDA
PB12.GPIOParameters=GPIO_Label
PB12.GPIO_Label=LEDA
PB12.Signal=GPIO_Output
PB13.GPIOParameters=GPIO_Label
PB13.GPIO_Label=LEDB
PB13.Signal=GPIO_Output
PB14.GPIOParameters=GPIO_Label
PB14.GPIO_Label=LEDC
PB14.Signal=GPIO_Output
PB15.GPIOParameters=GPIO_Label
PB15.GPIO_Label=LEDD
PB15.Signal=GPIO_Output
PB6.Mode=Asynchronous
PB6.Signal=USART1_TX
PB7.Mode=Asynchronous
PB7.Signal=USART1_RX
PB8.Mode=I2C
PB8.Signal=I2C1_SCL
PB9.Mode=I2C
PB9.Signal=I2C1_SDA
PC0.GPIOParameters=GPIO_Label
PC0.GPIO_Label=FCCRXA
PC0.Signal=GPIO_Input
PC1.GPIOParameters=GPIO_Label
PC1.GPIO_Label=FCCRXB
PC1.Signal=GPIO_Input
PC10.Mode=Asynchronous
PC10.Signal=USART3_TX
PC11.Mode=Asynchronous
PC11.Signal=USART3_RX
PC12.GPIOParameters=GPIO_Label
PC12.GPIO_Label=GPSPPS
PC12.Signal=GPIO_Input
PC13-ANTI_TAMP.GPIOParameters=GPIO_PuPd,GPIO_Label
PC13-ANTI_TAMP.GPIO_Label=GPSLNAEN
PC13-ANTI_TAMP.GPIO_PuPd=GPIO_PULLDOWN
PC13-ANTI_TAMP.Signal=GPIO_Output
PC14-OSC32_IN.GPIOParameters=GPIO_PuPd,GPIO_Label
PC14-OSC32_IN.GPIO_Label=GPSNRST
PC14-OSC32_IN.GPIO_PuPd=GPIO_PULLUP
PC14-OSC32_IN.Signal=GPIO_Output
PC2.GPIOParameters=GPIO_Label
PC2.GPIO_Label=FCCRXC
PC2.Signal=GPIO_Input
PC3.GPIOParameters=GPIO_Label
PC3.GPIO_Label=FCCRXD
PC3.Signal=GPIO_Input
PC4.GPIOParameters=GPIO_Label
PC4.GPIO_Label=FCCTXA
PC4.Signal=GPIO_Output
PC5.GPIOParameters=GPIO_Label
PC5.GPIO_Label=FCCTXB
PC5.Signal=GPIO_Output
PC6.GPIOParameters=GPIO_Label
PC6.GPIO_Label=FCCTXC
PC6.Signal=GPIO_Output
PC7.GPIOParameters=GPIO_Label
PC7.GPIO_Label=FCCTXD
PC7.Signal=GPIO_Output
PC9.Mode=I2C
PC9.Signal=I2C3_SDA
PH0-OSC_IN.Mode=HSE-External-Oscillator
PH0-OSC_IN.Signal=RCC_OSC_IN
PH1-OSC_OUT.Mode=HSE-External-Oscillator
PH1-OSC_OUT.Signal=RCC_OSC_OUT
RCC.HSE_VALUE=25000000
RCC.SYSCLKFreq_VALUE=168000000
RCC.SYSCLKSource=RCC_SYSCLKSOURCE_PLLCLK
board=custom

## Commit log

2019-12-02 Updated FIRWinSyncDesign.
    - Added different filter types (HP, BP, BS) .
    - Corrected passband gain.
    - Fixed impulse/step response plot.
2019-12-02 Updated FIR Filter Designer.
    - Added Time and Frequency Domain Data Export.
2019-12-02 Added two-state Kalman filter.
    - 'Hand-coded' two-state Kalman filter to estimate roll and pitch angles. Uses Euler angles.
2019-12-02 Added FIR and Kalman filter test.
    Arduino-based test for FIR filter and Kalman filter. Uses MPU9250.
2019-12-06 Hardware arrived. Added drivers, tests, etc...
    - Tested STM32F4 and STM32F7. Programmable via DFU.
    - Barometer driver.
    - Magnetometer driver.
    - IMU driver.
    - F4 25 MHz HSE seems to work.
    Also created Hades Micro schematic. Need to finish PCB layout and routing.
2019-12-08 Added TMP100 driver.
2019-12-09 Added H7 init code.
    - H7 HSE seems to be working.
2019-12-09 Added INA219 driver, printf for floats, changed IMU and magnetometer output units, re-mapped IMU axes.
    - INA219 current/voltage/power sensor connected to H7. Seems to display correct voltage (should test current and power..).
    - Can now print to UART with printf using floating point variables.
    - Changed magnetometer scaling to give unit vector.
    - Corrected accelerometer output to give units of m/s^2.
    - Gyroscope now outputs units of rad/s.
    - Re-mapped IMU axes to fit aircraft body coordinate system. Need to do same for magnetometer!
2019-12-10 Added brief hardware documentation, PCA9685 PWM driver.
    - Short presentation on general hardware design.
    - PCA9685 PWM driver to address all 8 servo/motor channels.
2019-12-11 Completed HadesMicro PCB. SWD works on F4.
    - Finalised board. Added Gerbers and assembly files.
    - Tested SWD via ST-LINK adapter and STM32F4 (NAVC). Debug works flawlessly in STM32CubeIDE.
2019-12-11 Changed folder structure.
2019-12-12 NMEA parser.
    - Added NMEA parser (tested only on host PC).
    - Works with GGA and RMC messages.
2019-12-13 Fixed IMU driver.
    - When checking the gyro's chipID, the I2C address and chipID register were still set to ACC not GYR!
2019-12-14 Added first NAVC FreeRTOS implementation.
2019-12-14 FIR filtering: NAVC sensor measurements. UAVDataLink: Transmitting debug data as bytes (COBS).
2019-12-14 NAVC Serial Debugger program (first version)
    - Implemented in C#. Reads packet-ed data sent from NAVC to debug serial output.
    - Decodes COBS messages successfully.
    - Need to implement data extraction and plotting.
    - Should decide on what data is sent via debug...
2019-12-15 Fixed data transfer to NAVC debug software. Added two-state Kalman filter.
    - NAVC debug software can now receive correct sensor/nav data from NAVC.
    - Kalman filter seems to work as expected. Needs more testing.
2019-12-15 Updated NAVC debug software.
    - Display navigation data in text form.
2019-12-16 Finished HADES micro hardware. Added README.
    - HADES micro files ready to be manufactured and (partially) assembled by JLCPCB.
    - README added.
2019-12-16 Updated README.
2019-12-16 Added hardware README.
2019-12-16 Added license to README.
2019-12-16 Create LICENSE
2019-12-16 Updated EKF folder.
2019-12-17 Updated Hades Micro (JLCPCB) silkscreen.
2019-12-17 NAVC debug software real-time plotting.
2019-12-19 Added temperature measurement, relayed back to NAVC data interface.
2019-12-19 DMA for GPS UART1 (NAVC).
    - DMA and FreeRTOS working to read GPS UART bytes.
2020-01-01 Hades Micro hardware arrived. Long development day..
    - Seems to work til now.
    - Wrote driver for BMX055.
    - Wrote basic RTOS structure.
    - Included Kalman filter for roll and pitch, complementary filter for yaw.
    BUG: SWD pin assignment on 10-pin 1.27mm pitch header!!!
2020-01-01 MPRLS SPI driver for Hades Micro.
2020-01-04 HADES Micro: RC PWM input. Definition file. Calibration.
2020-01-11 Added Hades schematic (PDF).
2020-05-19 Misc changes created by Unity...
2020-05-21 Started working on HADES NT: inexpensive, barebones, fixed-wing flight control hardware.
    STM32H7 + Quad SPI Flash + IMU + Magnetometer + Barometer + 8x RC IO + Various Interfaces + Power Monitoring
2020-07-04 EKF STM32F4 testbed.
2020-07-13 Finished HadesNT.
